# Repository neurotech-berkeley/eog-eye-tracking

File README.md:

# eog-eye-tracking
Exploration of EOG (electrooculogram) signals as a potential human computer interface.

## Project Description
This project was one of [Neurotech@Berkeley](https://github.com/neurotech-berkeley)'s Devices Division projects in Spring 2022. At Devices, we build hardware for the brain - to measure and analyze electrical signals generated by our bodies to see if we can come up with new ways to interact with computers. You can learn more about our organization as a whole at [neurotech.berkeley.edu](https://neurotech.berkeley.edu/).

Inspired by the potential that the gaze-tracking systems, we set out to explore a technique with substantially lower computational cost than computer vision: electrooculography (EOG). Unlike computer vision that relies on cameras, EOG relies on intrintic electric signals generated in our eye.

In this project, we prototyped, designed, fabricated, and tested analog front end (AFE) circuit to control a dinosaur chrome game. 

## Demo

In this demo, we connected our custom-designed PCB to a laptop through an Arduino. The dinosaur is controlled by blinks alone, hands and keyboard-free.

## Function Diagram

In this initial setup, we use three electrodes (2 attaching above and below an eye, and 1 fore reference behind an ear). These electrodes then attach to our PCB that amplify and filter from noise the difference between the two electrodes. The PCB is able to output a voltage acceptable by most 5V-operated microcontrollers (like Arduino, for example). The output of one channel is just an analog voltage that can be read by an onboard ADC on a microcontroller, which then can get transmitted to a laptop through a USB port for real-time analysis.

## Next Steps
Here are some potential improvements and ideas that we want to incorporate in future iterations of the design:

### 1. Add bluetooth capabilities
Currently, the PCB is communicating to the laptop through USB cable, but it would be cool to make it wireless! Open to exploring bluetooth chips other than Arduino. This would potentially mean exploring power consumption of the device and including a charging circuit.

### 2. Replace fixed resistors/capacitors with tunable alternatives
Currently, the AFE of our PCB is configured specifically for EOG signals, but it would be cool to make it adjustable to other types of signals by incorporating tunable resistors/capacitors in filters.

### 3. Incorporate a pattern recognition algorithm
Currently, we tell the difference between looking up and down by using basic thresholding :P

### 4. Build a chrome extension
Moving away from playing games, we want to explore incorporating eye tracking into an every-day workflow!

### 5. Build a dashboard for observing the signal in real-time

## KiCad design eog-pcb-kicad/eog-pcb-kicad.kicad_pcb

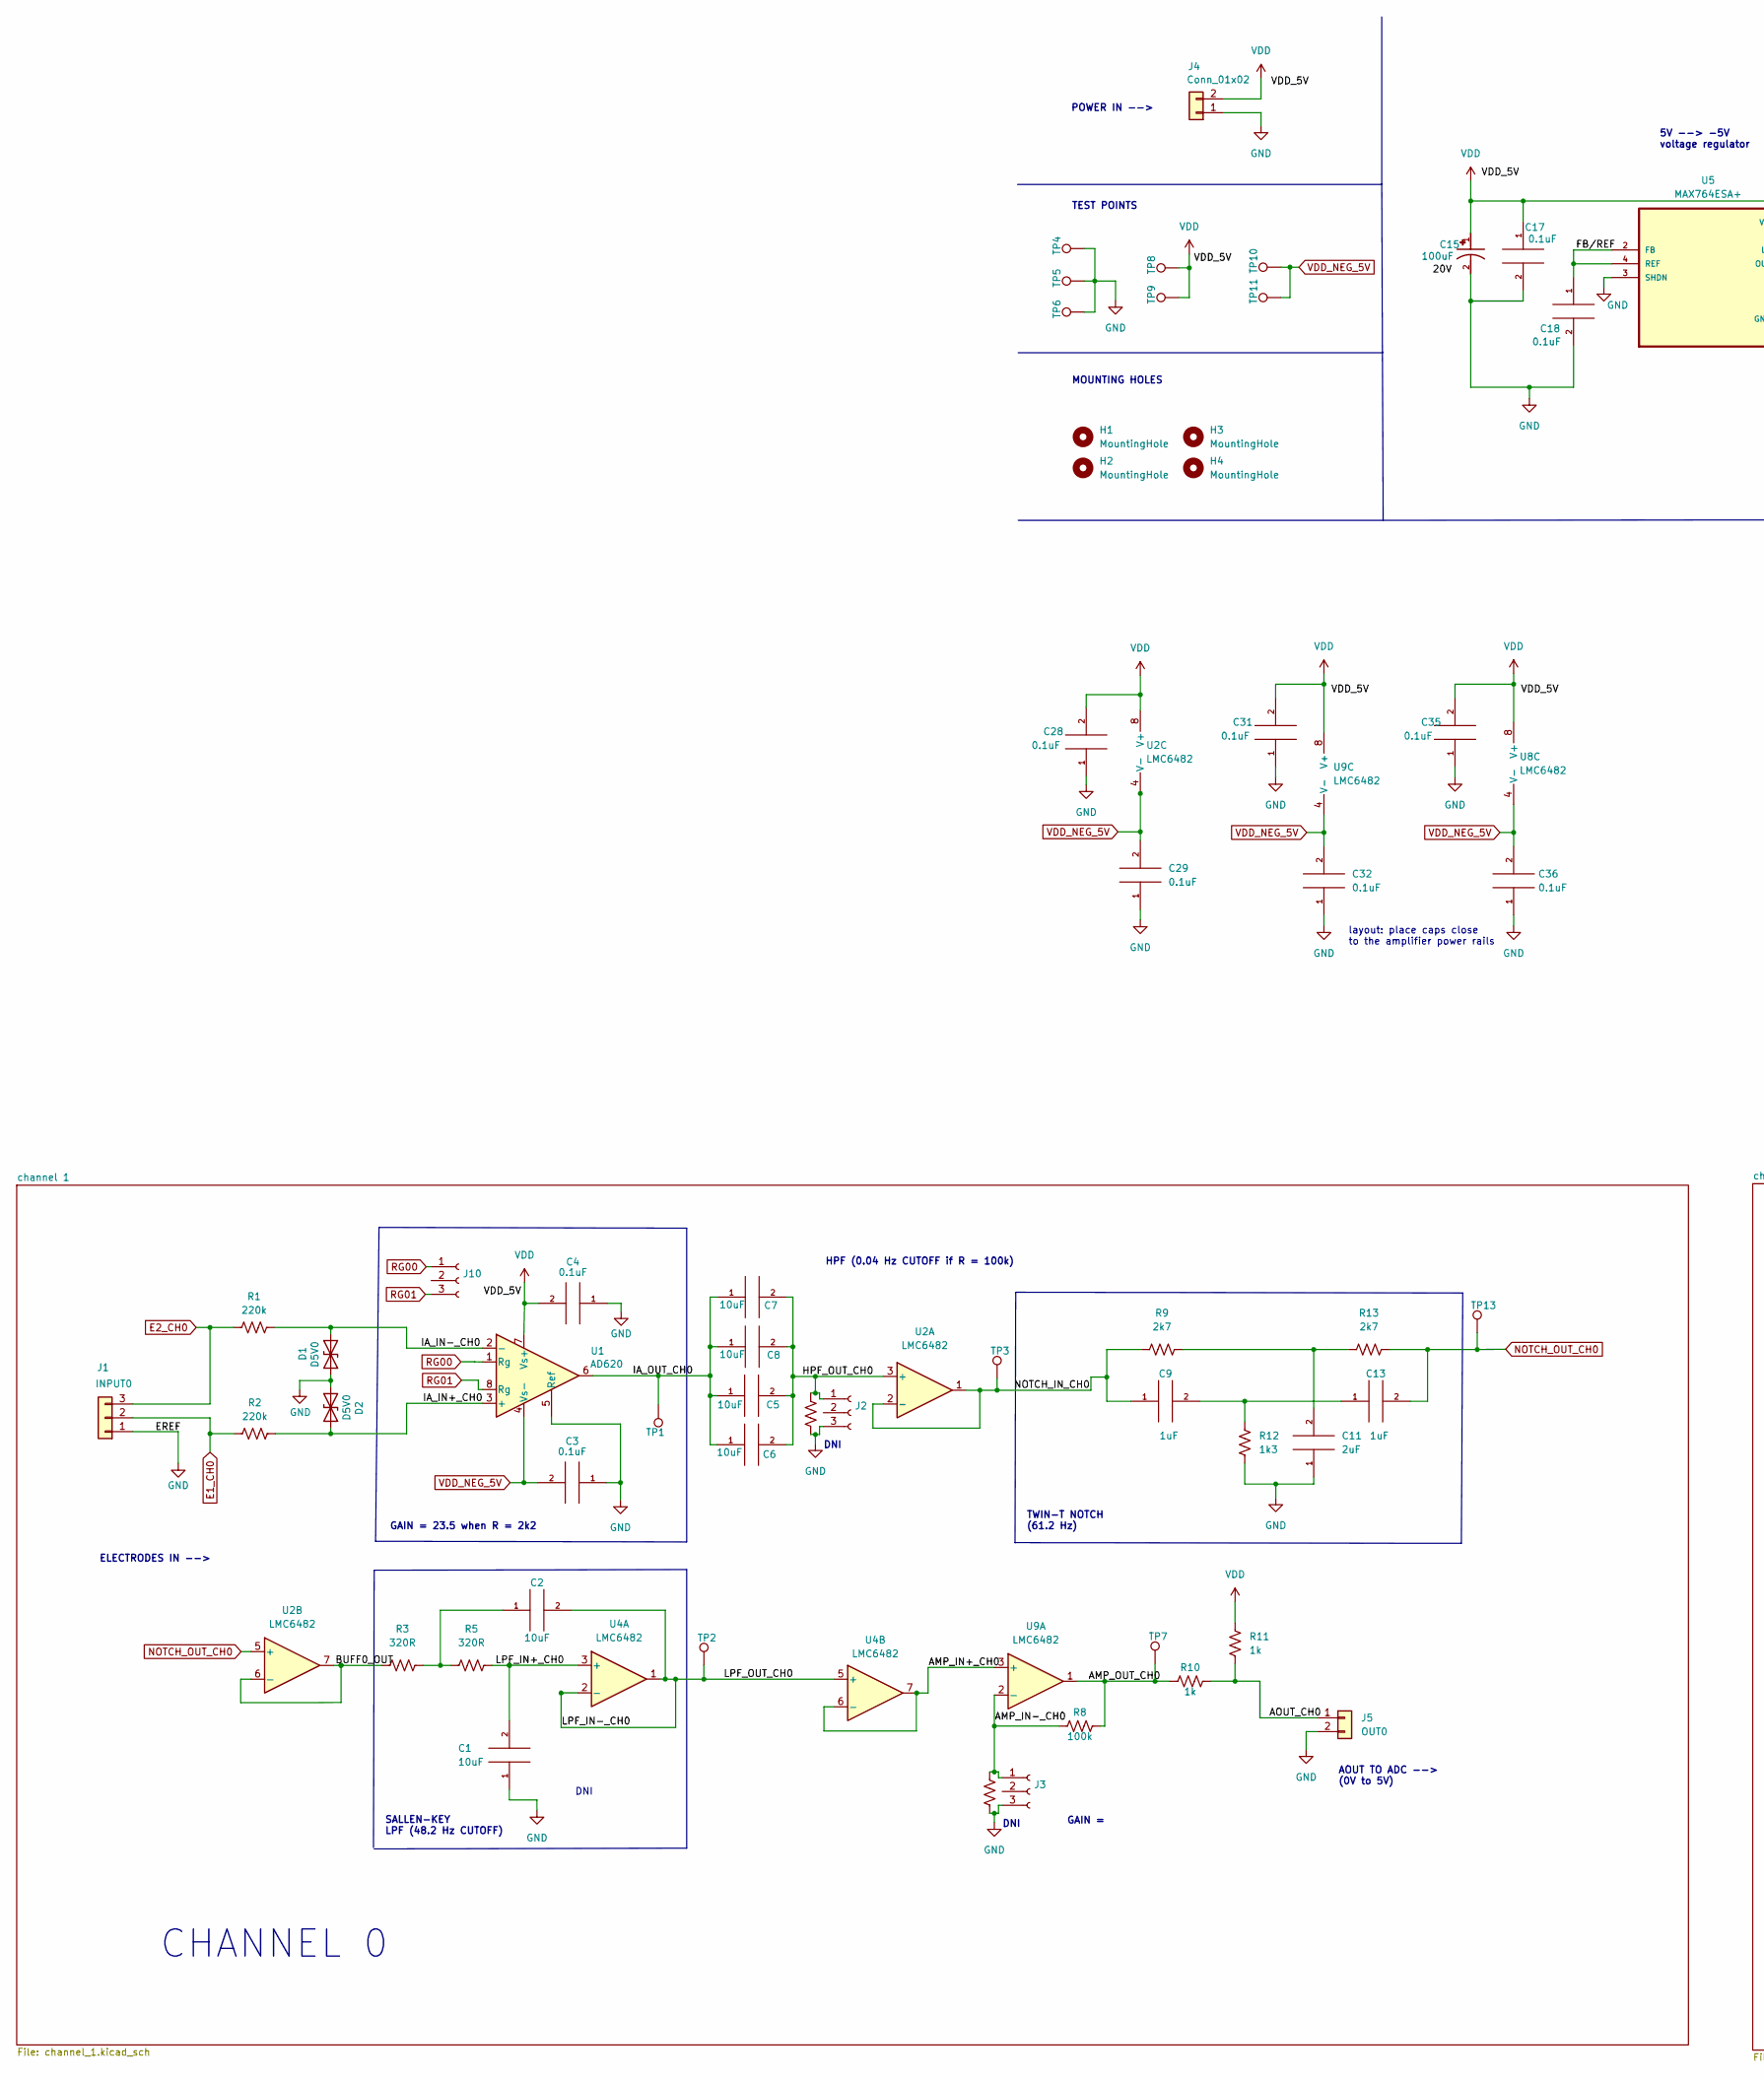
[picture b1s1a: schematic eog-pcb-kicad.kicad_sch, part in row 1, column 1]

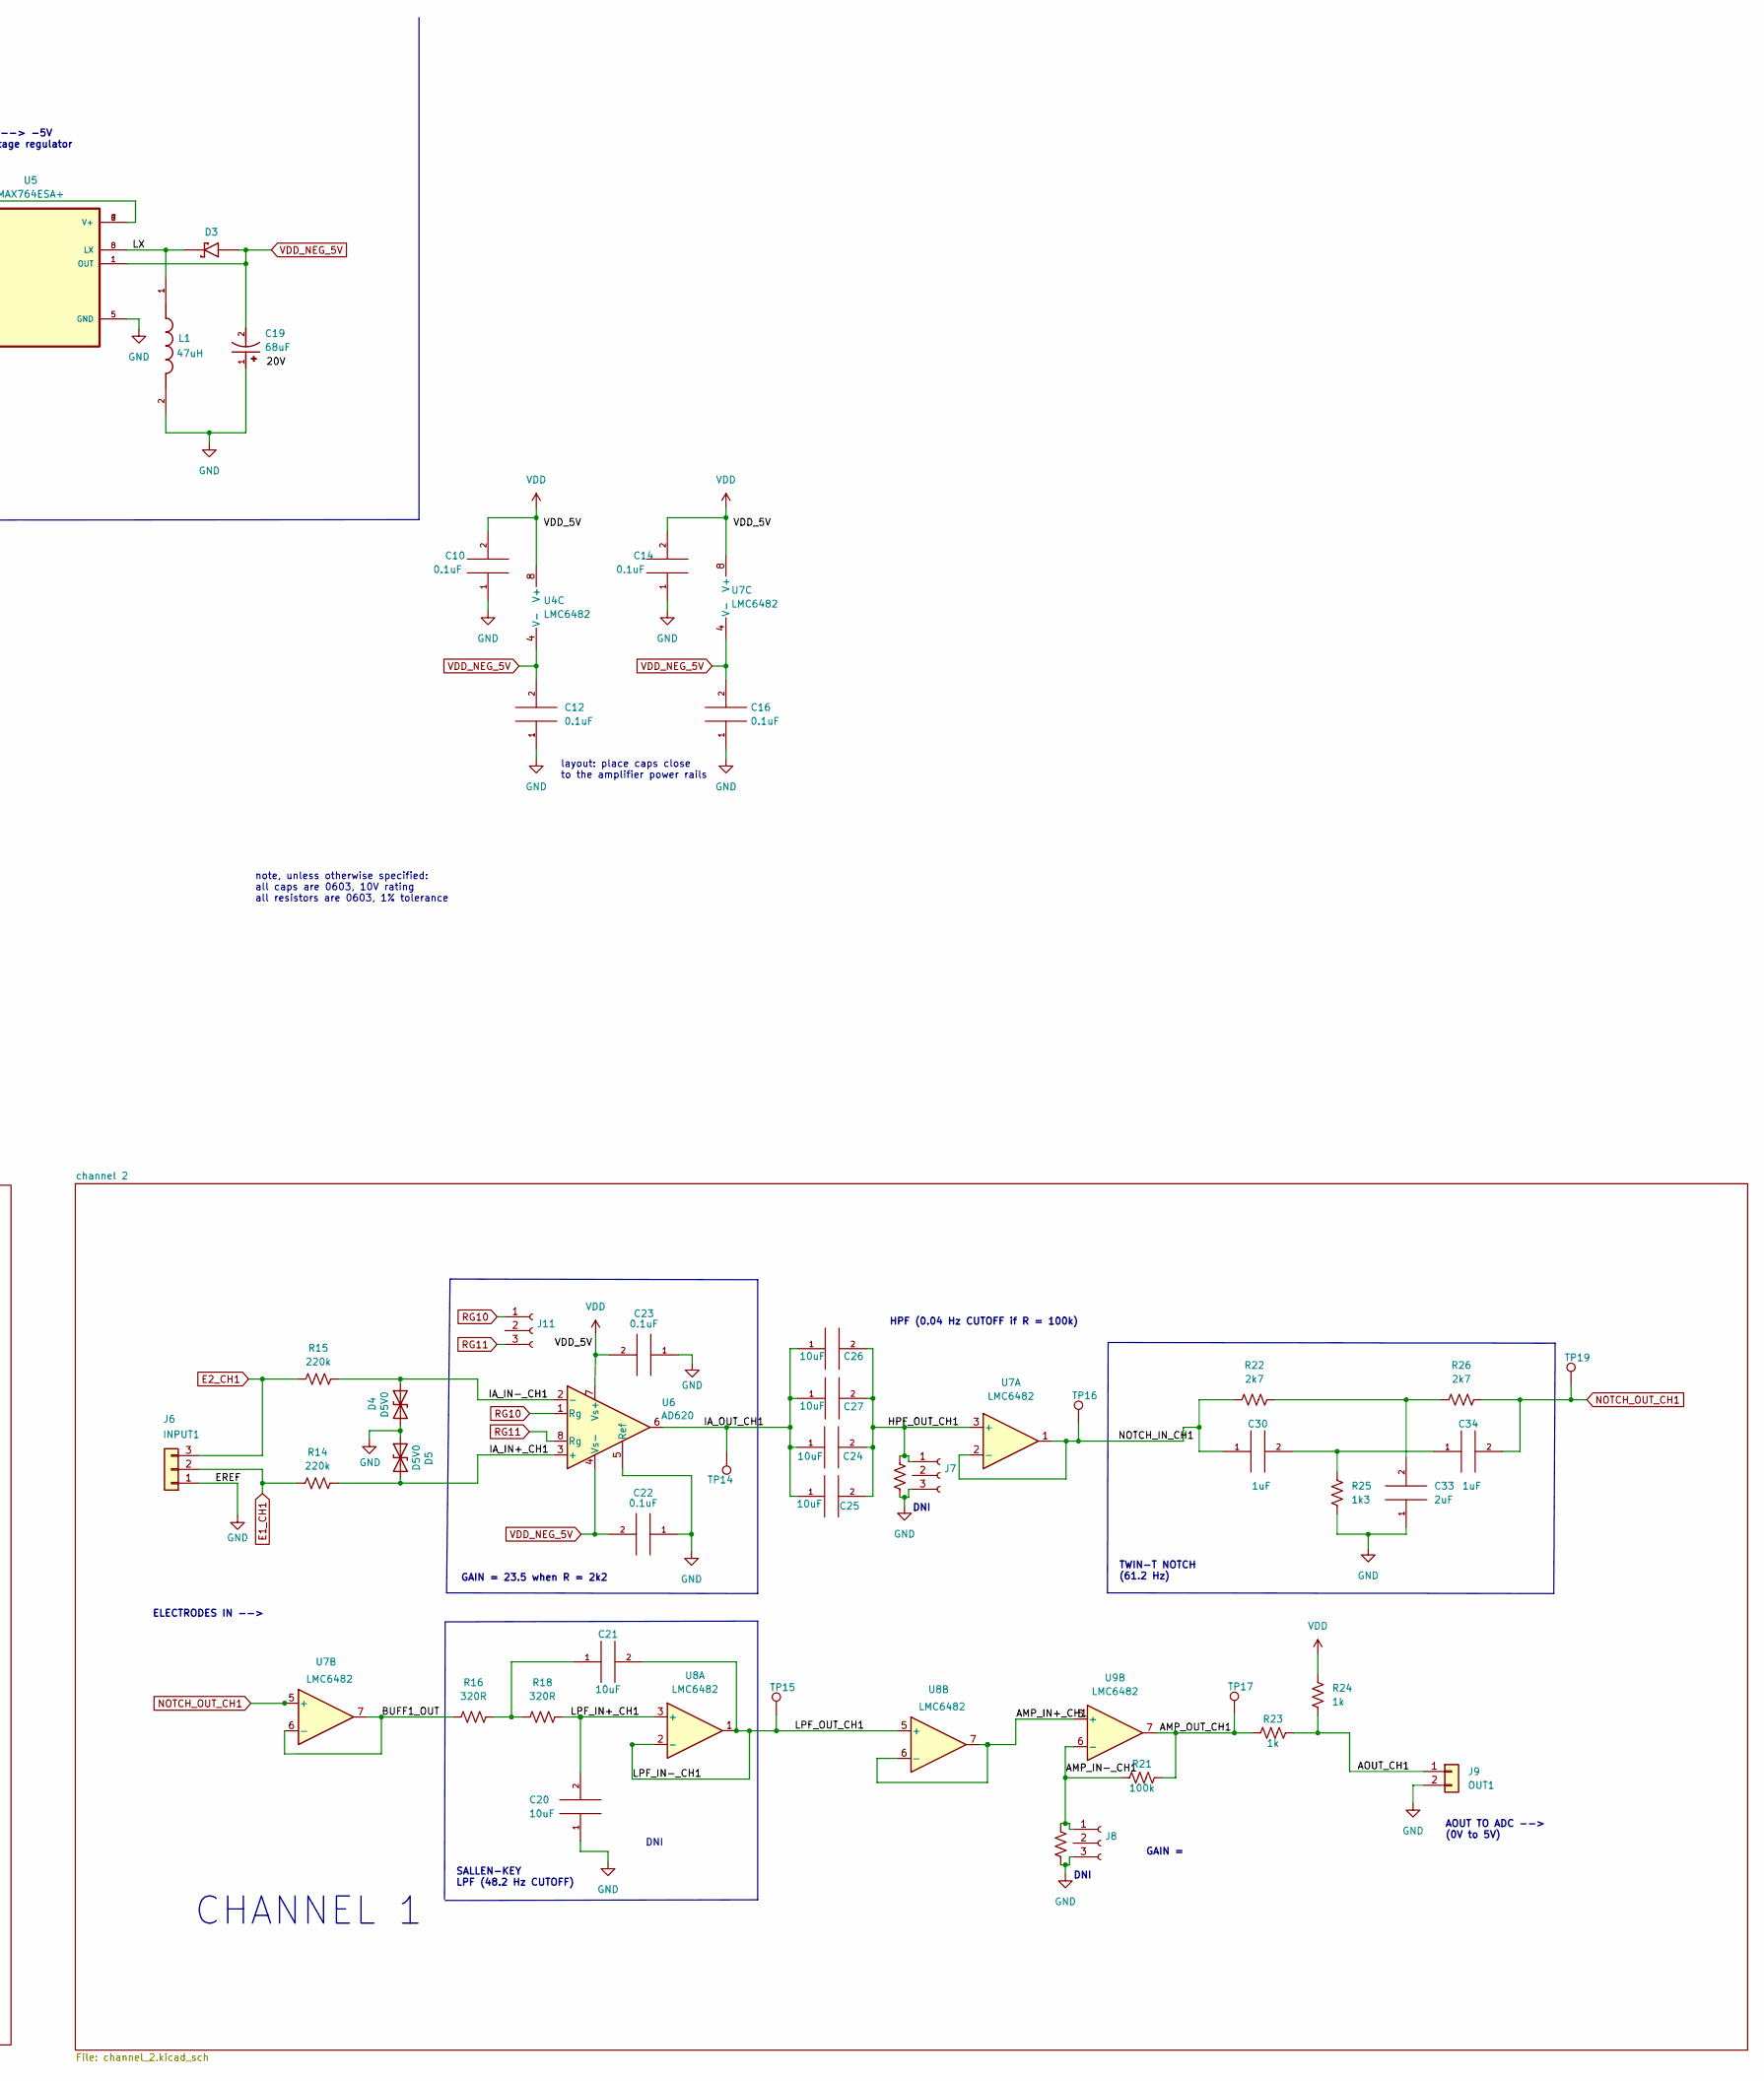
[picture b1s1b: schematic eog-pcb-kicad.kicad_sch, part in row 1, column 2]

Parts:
C1, C2, C5, C6, C7, C8, C20, C21, C24, C25, C26, C27: 10uF; C_0603_1608Metric
C3, C4, C10, C12, C14, C16, C17, C18, C22, C23, C28, C29, C31, C32, C35, C36: 0.1uF; C_0603_1608Metric
C9, C13, C30, C34: 1uF; C_0603_1608Metric
C11, C33: 2uF; C_0603_1608Metric
C15: 100uF; CAP_20TQC100MYF; PARTREV 30-Nov-20
C19: 68uF; CAP_20TQC100MYF; PARTREV 30-Nov-20
D1, D2, D4, D5: D5V0; R_0603_1608Metric
D3: MBRS330T3G; DIOM7959X261N; PARTREV 14
H1, H2, H3, H4: MountingHole; MountingHole_2.2mm_M2
J1: INPUT0; PinHeader_1x03_P2.54mm_Vertical
J2: HPF0; PinHeader_1x03_P2.54mm_Vertical
J3: G0; PinHeader_1x03_P2.54mm_Vertical
J4: Conn_01x02; PinHeader_1x02_P2.54mm_Vertical
J5: OUT0; PinHeader_1x02_P2.54mm_Vertical
J6: INPUT1; PinHeader_1x03_P2.54mm_Vertical
J7: HPF1; PinHeader_1x03_P2.54mm_Vertical
J8: G1; PinHeader_1x03_P2.54mm_Vertical
J9: OUT1; PinHeader_1x02_P2.54mm_Vertical
J10: RG0; PinHeader_1x03_P2.54mm_Vertical
J11: RG1; PinHeader_1x03_P2.54mm_Vertical
L1: 47uH; IND_NRS6028T470M; PARTREV N/A
R1, R2, R14, R15: 220k; R_0603_1608Metric
R3, R5, R16, R18: 320R; R_0603_1608Metric
R6, R7, R8, R19, R20, R21: 100k; R_0603_1608Metric
R9, R13, R22, R26: 2k7; R_0603_1608Metric
R10, R11, R23, R24: 1k; R_0603_1608Metric
R12, R25: 1k3; R_0603_1608Metric
TP1, TP2, TP3, TP4, TP5, TP6, TP7, TP8, TP9, TP10, TP11, TP13, TP14, TP15, TP16, TP17, TP19: TestPoint; TestPoint_Pad_1.0x1.0mm
U1, U6: AD620; SOIC-8_3.9x4.9mm_P1.27mm
U2, U4, U7, U8, U9: LMC6482; SOIC-8_3.9x4.9mm_P1.27mm
U5: MAX764ESA+; SOIC127P600X175-8N

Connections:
/AMP_IN+_CH0: U4.6 (-), U4.7, U9.3 (+)
/AMP_IN+_CH1: U8.6 (-), U8.7, U9.5 (+)
/AMP_IN-_CH0: J3.1, R7.2, R8.2, U9.2 (-)
/AMP_IN-_CH1: J8.1, R20.2, R21.2, U9.6 (-)
/AMP_OUT_CH0: R8.1, R10.2, TP7.1, U9.1
/AMP_OUT_CH1: R21.1, R23.2, TP17.1, U9.7
/AOUT_CH0: J5.1, R10.1, R11.1
/AOUT_CH1: J9.1, R23.1, R24.1
/BUFF0_OUT: R3.1, U2.6 (-), U2.7
/BUFF1_OUT: R16.1, U7.6 (-), U7.7
/FB/REF: C18.1, U5.2 (FB), U5.4 (REF)
/HPF_OUT_CH0: C5.2, C6.2, C7.2, C8.2, J2.1, R6.2, U2.3 (+)
/HPF_OUT_CH1: C24.2, C25.2, C26.2, C27.2, J7.1, R19.2, U7.3 (+)
/IA_IN+_CH0: D2.2 (A2), R2.2, U1.3 (+)
/IA_IN+_CH1: D5.2 (A2), R14.2, U6.3 (+)
/IA_IN-_CH0: D1.2 (A2), R1.2, U1.2 (-)
/IA_IN-_CH1: D4.2 (A2), R15.2, U6.2 (-)
/IA_OUT_CH0: C5.1, C6.1, C7.1, C8.1, TP1.1, U1.6
/IA_OUT_CH1: C24.1, C25.1, C26.1, C27.1, TP14.1, U6.6
/LPF_IN+_CH0: C1.2, R5.2, U4.3 (+)
/LPF_IN+_CH1: C20.2, R18.2, U8.3 (+)
/LPF_IN-_CH0: C2.2, TP2.1, U4.1, U4.2 (-), U4.5 (+)
/LPF_IN-_CH1: C21.2, TP15.1, U8.1, U8.2 (-), U8.5 (+)
/LX: D3.C, L1.1, U5.8 (LX)
/NOTCH_IN_CH0: C9.1, R9.2, TP3.1, U2.1, U2.2 (-)
/NOTCH_IN_CH1: C30.1, R22.2, TP16.1, U7.1, U7.2 (-)
E1_CH0: J1.2, R2.1
E1_CH1: J6.2, R14.1
E2_CH0: J1.3, R1.1
E2_CH1: J6.3, R15.1
GND: C1.1, C3.1, C4.1, C10.1, C11.1, C12.1, C14.1, C15.2, C16.1, C17.2, C18.2, C19.1, C20.1, C22.1, C23.1, C28.1, C29.1, C31.1, C32.1, C33.1, C35.1, C36.1, D1.1 (A1), D2.1 (A1), D4.1 (A1), D5.1 (A1), J1.1, J2.3, J3.3, J4.1, J5.2, J6.1, J7.3, J8.3, J9.2, L1.2, R6.1, R7.1, R12.2, R19.1, R20.1, R25.2, TP4.1, TP5.1, TP6.1, U1.5 (Ref), U5.3 (SHDN), U5.5 (GND), U6.5 (Ref)
NOTCH_OUT_CH0: C13.2, R13.1, TP13.1, U2.5 (+)
NOTCH_OUT_CH1: C34.2, R26.1, TP19.1, U7.5 (+)
unnamed: C2.1, R3.2, R5.1
unnamed: C11.2, R9.1, R13.2
unnamed: C9.2, C13.1, R12.1
unnamed: C21.1, R16.2, R18.1
unnamed: C30.2, C34.1, R25.1
unnamed: C33.2, R22.1, R26.2
RG00: J10.1, U1.1 (Rg)
RG01: J10.3, U1.8 (Rg)
RG10: J11.1, U6.1 (Rg)
RG11: J11.3, U6.8 (Rg)
VDD: C4.2, C10.2, C14.2, C15.1, C17.1, C23.2, C28.2, C31.2, C35.2, J4.2, R11.2, R24.2, TP8.1, TP9.1, U1.7 (Vs+), U2.8 (V+), U4.8 (V+), U5.6 (V+), U5.7 (V+), U6.7 (Vs+), U7.8 (V+), U8.8 (V+), U9.8 (V+)
VDD_NEG_5V: C3.2, C12.2, C16.2, C19.2, C22.2, C29.2, C32.2, C36.2, D3.A, TP10.1, TP11.1, U1.4 (Vs-), U2.4 (V-), U4.4 (V-), U5.1 (OUT), U6.4 (Vs-), U7.4 (V-), U8.4 (V-), U9.4 (V-)

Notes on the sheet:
DNI
GAIN = 23.5 when R = 2k2
ELECTRODES IN -->
GAIN = 23.5 when R = 2k2
CHANNEL 1
TWIN-T NOTCH (61.2 Hz)
AOUT TO ADC --> (0V to 5V)
POWER IN -->
TEST POINTS
MOUNTING HOLES
layout: place caps close to the amplifier power rails
CHANNEL 0
GAIN =
note, unless otherwise specified: all caps are 0603, 10V rating all resistors are 0603, 1% tolerance
HPF (0.04 Hz CUTOFF if R = 100k)
GAIN =
5V --> -5V voltage regulator
SALLEN-KEY LPF (48.2 Hz CUTOFF)

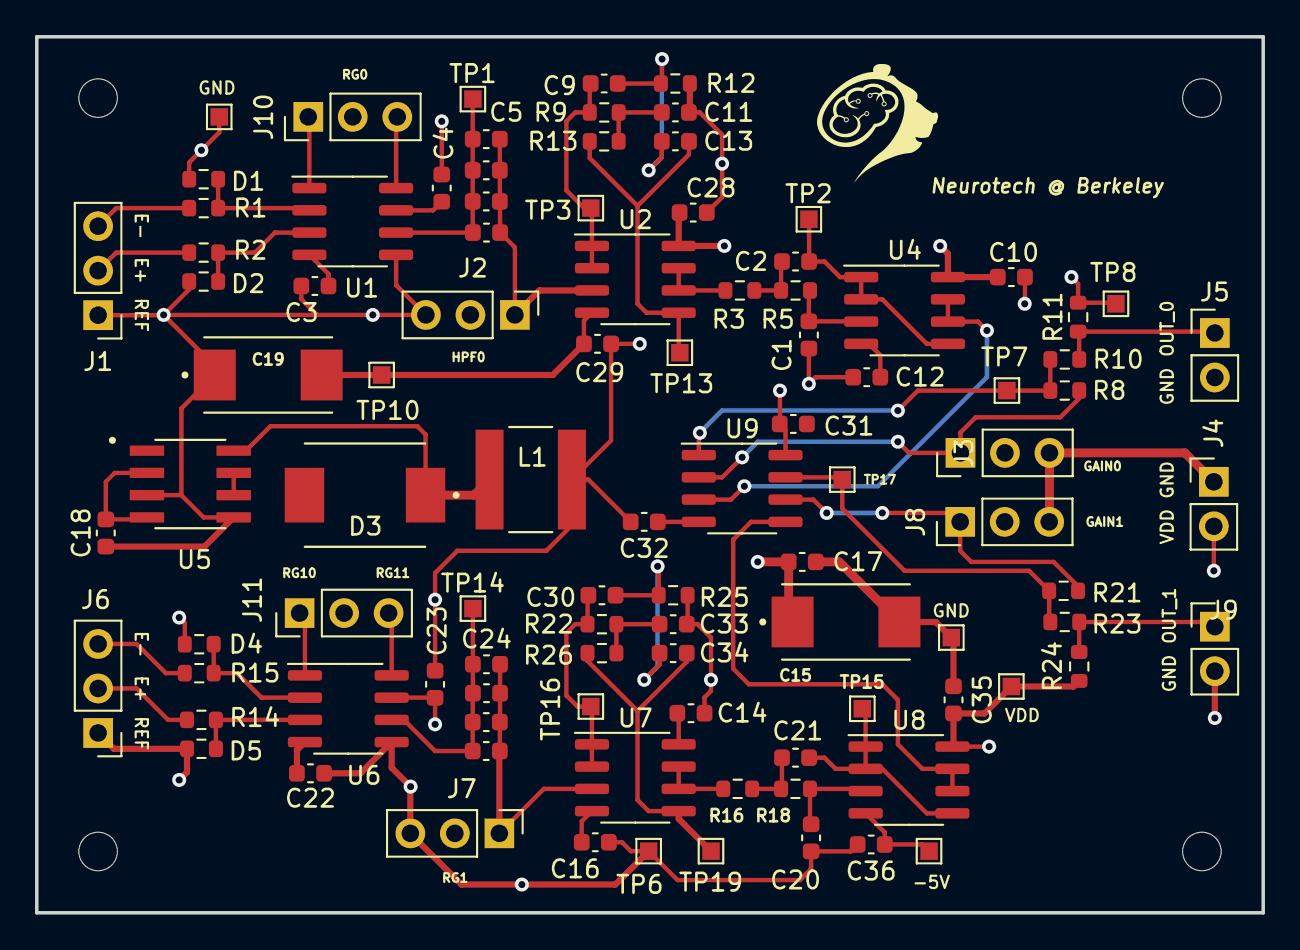
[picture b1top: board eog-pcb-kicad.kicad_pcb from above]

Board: 4 copper layers, 70.0 x 50.0 mm, 102 parts (0 on the bottom side), 45 nets.

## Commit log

2022-08-21 adding PCB and production files
2022-08-21 adding firmware files to upload to Arduino
2022-08-25 included future improvements and ideas to the README
2022-10-28 adding collection script
2022-10-30 add calibration testing
2022-11-18 added libraries for digipots and started reorganizing the pcb for 2nd version
2022-11-23 progress on layout
2022-12-28 gen2 board is ready and production files are generated
2022-12-28 updating BOM and CPL files
2023-01-08 adding the arduino script for testing new pcb boards
2023-02-25 bluetooth prog
2023-03-03 updated the schematics with buffer op-amp and resistor sockets
2023-03-04 preliminary layout and added libraries
2023-03-04 layout is 90 percent done
2023-03-06 added framework for grpc
2023-03-20 grpc infra complete
2023-04-09 Merge
